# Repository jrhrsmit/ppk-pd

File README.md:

<div align="center">

# PPK-PD

<br/>

Power profiler kit with USB power delivery and current/voltage limiting
capabilities.

</div>

## About

<div align="center">

</div>

TODO: description
This project is an attempt at recreating the Nordic Power Profiler Kit with
some improvements:
 - USB-C connector
 - USB Power Delivery (20V - 5A)
 - Higher samplerate
 - Easily scritable interface
 - Current and voltage limiting
 - Voltage as well as current measuring
 - Remote voltage sensing

This project is build with the open-source EDA [faebryk](https://github.com/faebryk/faebryk).

## What can you do with this project?

This project can be completely ordered and assembled by 
[JLCPCB](https://jlcpcb.com).
Releases are pending.

## Working with the source files

See [here](./docs/development.md) for the instructions on how to install and edit this project.

## Building

If you want to build the physical output of this project you can find the build instructions [here](./docs/build_instructions.md).

## Contributing

If you want to share your alterations, improvements, or add bugfixes to this project, please take a look at the [contributing guidelines](./docs/CONTRIBUTING.md).

## Community Support

Community support is provided via Discord; see the Resources below for details.

### Resources

- Source Code: [https://github.com/jrhrsmit/ppk-pd](https://github.com/jrhrsmit/ppk-pd)
- Chat: Real-time chat happens in faebryk's Discord Server (chit-chat room for now). Use this Discord [Invite](https://discord.gg/95jYuPmnUW) to register
- Issues: [https://github.com/jrhrsmit/ppk-pd/issues](https://github.com/jrhrsmit/ppk-pd/issues)

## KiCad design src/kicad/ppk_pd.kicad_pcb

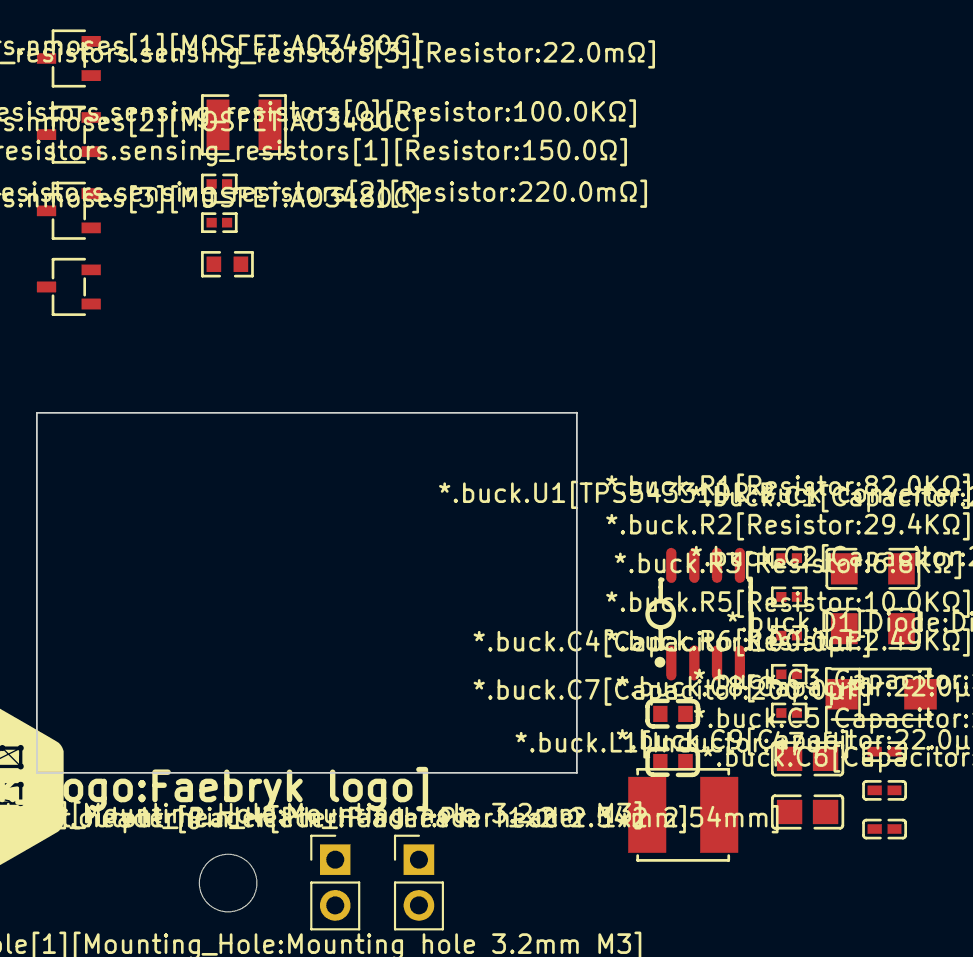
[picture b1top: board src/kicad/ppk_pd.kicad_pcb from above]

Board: 2 copper layers, 32 parts (0 on the bottom side), 10 nets, no tracks yet.

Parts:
*.auto_sense_resistors.nmoses[0][MOSFET:AO3480C], *.auto_sense_resistors.nmoses[1][MOSFET:AO3480C], *.auto_sense_resistors.nmoses[2][MOSFET:AO3480C], *.auto_sense_resistors.nmoses[3][MOSFET:AO3480C]: AO3480C; SOT-23-3_L2.9-W1.6-P1.90-LS2.8-BR
*.auto_sense_resistors.sensing_resistors[0][Resistor:100.0KΩ]: 100.0KΩ; R0402
*.auto_sense_resistors.sensing_resistors[1][Resistor:150.0Ω]: 150.0Ω; R0402
*.auto_sense_resistors.sensing_resistors[2][Resistor:220.0mΩ]: 220.0mΩ; R0603
*.auto_sense_resistors.sensing_resistors[3][Resistor:22.0mΩ]: 22.0mΩ; R1210
*.buck.C1[Capacitor:2.2µF], *.buck.C2[Capacitor:2.2µF]: 2.2µF; C1206
*.buck.C3[Capacitor:10.0µF], *.buck.C5[Capacitor:10.0µF]: 10.0µF; C0402
*.buck.C4[Capacitor:100.0µF]: 100.0µF; C0603
*.buck.C6[Capacitor:4.7µF]: 4.7µF; C0402
*.buck.C7[Capacitor:200.0µF]: 200.0µF; C0603
*.buck.C8[Capacitor:22.0µF], *.buck.C9[Capacitor:22.0µF]: 22.0µF; C0805
*.buck.D1[Diode:Diode]: Diode; SMA_L4.4-W2.6-LS5.0-RD
*.buck.L1[Inductor:47uH]: 47uH; IND-SMD_L5.0-W5.0
*.buck.R1[Resistor:82.0KΩ]: 82.0KΩ; R0402
*.buck.R2[Resistor:29.4KΩ]: 29.4KΩ; R0402
*.buck.R3[Resistor:6.8KΩ]: 6.8KΩ; R0402
*.buck.R5[Resistor:10.0KΩ]: 10.0KΩ; R0402
*.buck.R6[Resistor:2.49KΩ]: 2.49KΩ; R0402
*.buck.U1[TPS54331DR:Buck converter]: Buck converter; SOIC-8_L5.0-W4.0-P1.27-LS6.0-BL
*.faebryk_logo[Faebryk_Logo:Faebryk logo]: Faebryk logo; faebryk_logo
*.input_header[Pin_Header:Pin header 1x2 2.54mm], *.output_header[Pin_Header:Pin header 1x2 2.54mm]: Pin header 1x2 2.54mm; PinHeader_1x02_P2.54mm_Vertical
*.mounting_hole[0][Mounting_Hole:Mounting hole 3.2mm M3], *.mounting_hole[1][Mounting_Hole:Mounting hole 3.2mm M3], *.mounting_hole[2][Mounting_Hole:Mounting hole 3.2mm M3], *.mounting_hole[3][Mounting_Hole:Mounting hole 3.2mm M3]: Mounting hole 3.2mm M3; MountingHole_3.2mm_M3_ISO7380

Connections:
*.buck.C1[Capacitor:2.2µF]-*.buck.R1[Resistor:82.0KΩ]-*.buck.C3[Capacitor:10.0µ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: *.buck.C1[Capacitor:2.2µF].2, *.buck.C2[Capacitor:2.2µF].2, *.buck.C3[Capacitor:10.0µF].2, *.buck.R1[Resistor:82.0KΩ].2, *.buck.U1[TPS54331DR:Buck converter].2
*.buck.C4[Capacitor:100.0µF]-*.buck.U1[TPS54331DR:Buck converter]: *.buck.C4[Capacitor:100.0µF].2, *.buck.U1[TPS54331DR:Buck converter].1
*.buck.C4[Capacitor:100.0µF]-*.buck.U1[TPS54331DR:Buck converter]-*.buck.D1[Dio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: *.buck.C4[Capacitor:100.0µF].1, *.buck.D1[Diode:Diode].1, *.buck.L1[Inductor:47uH].1, *.buck.U1[TPS54331DR:Buck converter].8
*.buck.C7[Capacitor:200.0µF]-*.buck.U1[TPS54331DR:Buck converter]-*.buck.C6[Cap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: *.buck.C6[Capacitor:4.7µF].2, *.buck.C7[Capacitor:200.0µF].2, *.buck.U1[TPS54331DR:Buck converter].6
*.buck.C9[Capacitor:22.0µF]-*.buck.R5[Resistor:10.0KΩ]-*.buck.C8[Capacitor:22.0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: *.buck.C8[Capacitor:22.0µF].2, *.buck.C9[Capacitor:22.0µF].2, *.buck.L1[Inductor:47uH].2, *.buck.R5[Resistor:10.0KΩ].2
*.buck.R2[Resistor:29.4KΩ]-*.buck.R6[Resistor:2.49KΩ]-*.buck.C1[Capacitor:2.2µF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: *.buck.C1[Capacitor:2.2µF].1, *.buck.C2[Capacitor:2.2µF].1, *.buck.C3[Capacitor:10.0µF].1, *.buck.C5[Capacitor:10.0µF].1, *.buck.C7[Capacitor:200.0µF].1, *.buck.C8[Capacitor:22.0µF].1, *.buck.C9[Capacitor:22.0µF].1, *.buck.D1[Diode:Diode].2, *.buck.R2[Resistor:29.4KΩ].1, *.buck.R3[Resistor:6.8KΩ].1, *.buck.R6[Resistor:2.49KΩ].1, *.buck.U1[TPS54331DR:Buck converter].7
*.buck.R2[Resistor:29.4KΩ]-*.buck.U1[TPS54331DR:Buck converter]-*.buck.R1[Resis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: *.buck.R1[Resistor:82.0KΩ].1, *.buck.R2[Resistor:29.4KΩ].2, *.buck.U1[TPS54331DR:Buck converter].3
*.buck.R3[Resistor:6.8KΩ]-*.buck.C6[Capacitor:4.7µF]: *.buck.C6[Capacitor:4.7µF].1, *.buck.R3[Resistor:6.8KΩ].2
*.buck.R6[Resistor:2.49KΩ]-*.buck.R5[Resistor:10.0KΩ]-*.buck.U1[TPS54331DR:Buck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: *.buck.R5[Resistor:10.0KΩ].1, *.buck.R6[Resistor:2.49KΩ].2, *.buck.U1[TPS54331DR:Buck converter].5
*.buck.U1[TPS54331DR:Buck converter]-*.buck.C5[Capacitor:10.0µF]: *.buck.C5[Capacitor:10.0µF].2, *.buck.U1[TPS54331DR:Buck converter].4

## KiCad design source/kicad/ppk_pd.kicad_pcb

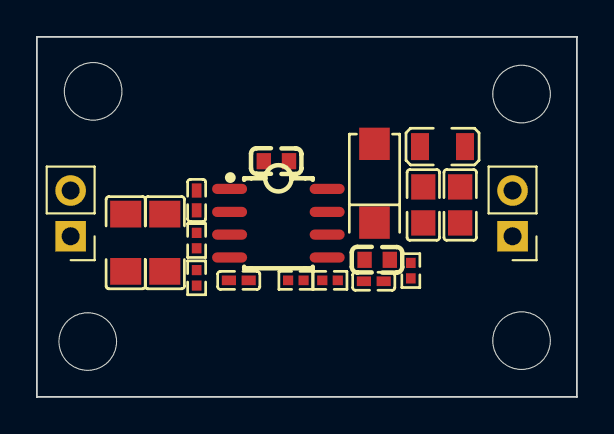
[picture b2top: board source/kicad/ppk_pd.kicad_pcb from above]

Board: 2 copper layers, 30.0 x 20.0 mm, 23 parts (0 on the bottom side), 10 nets, no tracks yet.

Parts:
buck.C1[Capacitor:2.2uF], buck.C2[Capacitor:2.2uF]: 2.2uF; C1206
buck.C3[Capacitor:10nF], buck.C5[Capacitor:10nF]: 10nF; C0402
buck.C4[Capacitor:100nF]: 100nF; C0603
buck.C6[Capacitor:4.7nF]: 4.7nF; C0402
buck.C7[Capacitor:200pF]: 200pF; C0603
buck.C8[Capacitor:22uF], buck.C9[Capacitor:22uF]: 22uF; C0805
buck.D1[Diode:D]: D; SMA_L4.4-W2.6-LS5.0-RD
buck.L1[Inductor:47uH]: 47uH; IND-SMD_L2.5-W2.0-A
buck.R1[Resistor:82k]: 82k; R0402
buck.R2[Resistor:29.4k]: 29.4k; R0402
buck.R3[Resistor:6.8k]: 6.8k; R0402
buck.R5[Resistor:10k]: 10k; R0402
buck.R6[Resistor:2.49k]: 2.49k; R0402
buck.U1[TPS54331DR:U]: U; SOIC-8_L5.0-W4.0-P1.27-LS6.0-BL
input_header[Pin_Header:J]: J; PinHeader_1x02_P2.54mm_Vertical
mounting_hole[0][Mounting_Hole:H], mounting_hole[1][Mounting_Hole:H], mounting_hole[2][Mounting_Hole:H], mounting_hole[3][Mounting_Hole:H]: H; MountingHole_3.2mm_M3_ISO7380
output_header[Pin_Header:J]: J; PinHeader_1x02_P2.54mm_Vertical

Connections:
buck.C6[Capacitor:4.7nF]-buck.R3[Resistor:6.8k]: buck.C6[Capacitor:4.7nF].2, buck.R3[Resistor:6.8k].1
buck.R1[Resistor:82k]-buck.R2[Resistor:29.4k]-buck.U1[TPS54331DR:U]: buck.R1[Resistor:82k].2, buck.R2[Resistor:29.4k].1, buck.U1[TPS54331DR:U].3
buck.U1[TPS54331DR:U]-buck.C4[Capacitor:100nF]: buck.C4[Capacitor:100nF].1, buck.U1[TPS54331DR:U].1
buck.U1[TPS54331DR:U]-buck.C5[Capacitor:10nF]: buck.C5[Capacitor:10nF].1, buck.U1[TPS54331DR:U].4
buck.U1[TPS54331DR:U]-buck.C6[Capacitor:4.7nF]-buck.C7[Capacitor:200pF]: buck.C6[Capacitor:4.7nF].1, buck.C7[Capacitor:200pF].1, buck.U1[TPS54331DR:U].6
buck.U1[TPS54331DR:U]-buck.D1[Diode:D]-buck.C4[Capacitor:100nF]-buck.L1[Inducto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: buck.C4[Capacitor:100nF].2, buck.D1[Diode:D].2, buck.L1[Inductor:47uH].1, buck.U1[TPS54331DR:U].8
buck.U1[TPS54331DR:U]-buck.R5[Resistor:10k]-buck.R6[Resistor:2.49k]: buck.R5[Resistor:10k].2, buck.R6[Resistor:2.49k].1, buck.U1[TPS54331DR:U].5
buck[Buck_Converter_TPS54331DR:virt]: buck.C1[Capacitor:2.2uF].1, buck.C2[Capacitor:2.2uF].1, buck.C3[Capacitor:10nF].1, buck.R1[Resistor:82k].1, buck.U1[TPS54331DR:U].2, input_header[Pin_Header:J].2
buck[Buck_Converter_TPS54331DR:virt]:3: buck.C8[Capacitor:22uF].1, buck.C9[Capacitor:22uF].1, buck.L1[Inductor:47uH].2, buck.R5[Resistor:10k].1, output_header[Pin_Header:J].2
buck[Buck_Converter_TPS54331DR:virt]:4-buck[Buck_Converter_TPS54331DR:virt]:2: buck.C1[Capacitor:2.2uF].2, buck.C2[Capacitor:2.2uF].2, buck.C3[Capacitor:10nF].2, buck.C5[Capacitor:10nF].2, buck.C7[Capacitor:200pF].2, buck.C8[Capacitor:22uF].2, buck.C9[Capacitor:22uF].2, buck.D1[Diode:D].1, buck.R2[Resistor:29.4k].2, buck.R3[Resistor:6.8k].2, buck.R6[Resistor:2.49k].2, buck.U1[TPS54331DR:U].7, input_header[Pin_Header:J].1, output_header[Pin_Header:J].1

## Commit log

2023-06-16 Use latest Faebryk
2023-06-16 Update license
2023-06-17 Make empty classes, add part pickers, components, LCSC, add easyeda at requirements
2023-06-28 add parallelism in fetch.sh for jlcpcb db
2023-06-28 add si_prefix and typer as requirements
2023-06-28 add tolerance trait to capacitor
2023-06-28 Add resistor (same as faebryk, but with tolerance)
2023-06-28 add TPS54331DR boost converter
2023-06-28 fix main.py
    Setup typer, copy write_netlist from CableTester, remove unused code
2023-06-28 Add JLCPCB db search
    Add JLCPCB SQL db search for Capacitor, Resistor, and partnumber
    Move code from lcsc.py to jlcpcb/partnumber.py
    Rename ppk-pd to ppk_pd
2023-06-28 ignore JLCPCB db files
2023-06-28 Add range queries for Capacitors, add TPS54331 PN
2023-06-29 move jlcpcb utilities to util, fix searching for ranges
2023-06-29 Update gitignore, create new kicad7 prj
2023-06-29 Improve buck converter, improve capacitor and resistor classes
    Add rated voltage query for Capacitor JLCPCB search
    Add case size and auto case size selection for Capacitor
    Add case size to Resistor
    Move E series to e_series.py
    Buck: Add calculation of output voltage div
    Buck: Add calculation of input capacitors
2023-06-29 move e_series_in_range to e_series.py, fix some case_size issues
2023-07-01 Fix JLCPCB query sorting, fix bugs in capacitor nF value finding, add size queries
2023-07-01 fix resistor case sizes, add PN to diode, fix boot cap at 100nF
2023-07-02 Add inductor search and selection in buck
    add missing type desc for diode
    strip units in si_to_float
2023-07-02 Add compensation filter calc
2023-07-02 add inductor search
2023-07-02 add DC bias capacitance error in compensation filter calc
2023-07-02 Fix catching no search results, less logging
2023-07-02 fine tuning of buck calculations, print results
2023-07-02 fine tune buck some more, check output voltage of buck
2023-07-02 attempt to download jlcpcb db if it doesn't exist
2023-07-02 update datasheet link
2023-07-07 Better logging, add header and try adding designators
2023-09-03 update to faebryk master
2023-09-18 Add E12, E6, and E3 series
2023-09-18 ignore more kicad files
2023-09-18 fix resistor/inductor search, add power dissipation, update MOSFET
2023-09-18 add automatic sensing resistor selection
2023-09-26 Add MOSFET search, add auto pinmapping feature
2023-10-14 add script that removes designators
2023-10-14 Add jlcpcb_db function that executes the SQL queries and handles the database
2023-10-14 Add tolerance filtering in extra field
2023-11-13 move auto pinmapping to own file
2023-11-13 start on tortoise
2024-01-27 refactor for new faebry, wip

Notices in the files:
README.md:
License: MIT
